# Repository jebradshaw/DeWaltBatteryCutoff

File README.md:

# DeWaltBatteryCutoff
Please Note: This circuit is purely experimental. There has not been much testing on it - at all.

PCB using the RP2040 Pico microcontroller to monitor a 20V DeWalt battery and give an alarm and eventually shutoff the battery load to avoid deep discharging.

KiCAD PCB Design
I used the pico microcontroller KiCAD model from https://github.com/ncarandini/KiCad-RP-Pico, which is really nicely done!

The circuit uses a RP2040 Pico microcontroller to monitor the battery voltage from a buffered voltage divider on an ADC pin.  The user must turn on the board with an external temporary pushbutton and power MOSFET turns on supplying voltage to the regulator that turns on the pico microcontroller.  The Pico then latches the MOSFET on and begins to run the voltage monitoring program. When the battery reaches a set value (can be stored in EEPROM) a buzzer alarm begins to sound, getting more rapid as the battery voltage approaches the low voltage cutoff value.  Once that value is surpassed (with hysteresis) a 10 second timer begins and the output voltage is cutoff using a P-Channel MOSFET (currently using a 27 amp version FRP27P06) where the pico turns itself off.  Data is transmitted over the USB port at 115200 baud and eeprom values can be set and saved.  Output format is a serial ASCII string with the following format:

NAME, TIME, rate of discharge, battery voltage, Buzzer critical state, high voltage alarm, low voltage alarm

"PICOBATMON,T:3412691,dVdT:0.000,Bv:20.24,Bcrit:0,Halarm:17.50,Lalarm:17.00\r\n"

The control program was written using the Arduino IDE with the Raspberry Pi Pico/RP2040 board library.  The user can set and save specific parameters in the EEPROM such as voltage, gain (resistor divider ratio), and a brief description (string).

Schematic of microcontroller circuit above.  PDF of Schematic can be downloaded here-> [PicoDeWalt_BattMonV2 Schematic.pdf](https://github.com/jebradshaw/DeWaltBatteryCutoff/files/11053368/PicoDeWalt_BattMonV2.Schematic.pdf)
 .

These printed circuit boards were made using Digikeys DK Red service and I am very happy with the results.

 To do list:  
   1. Turn on and off debugging through serial output terminal
   2. Implement Checksum?

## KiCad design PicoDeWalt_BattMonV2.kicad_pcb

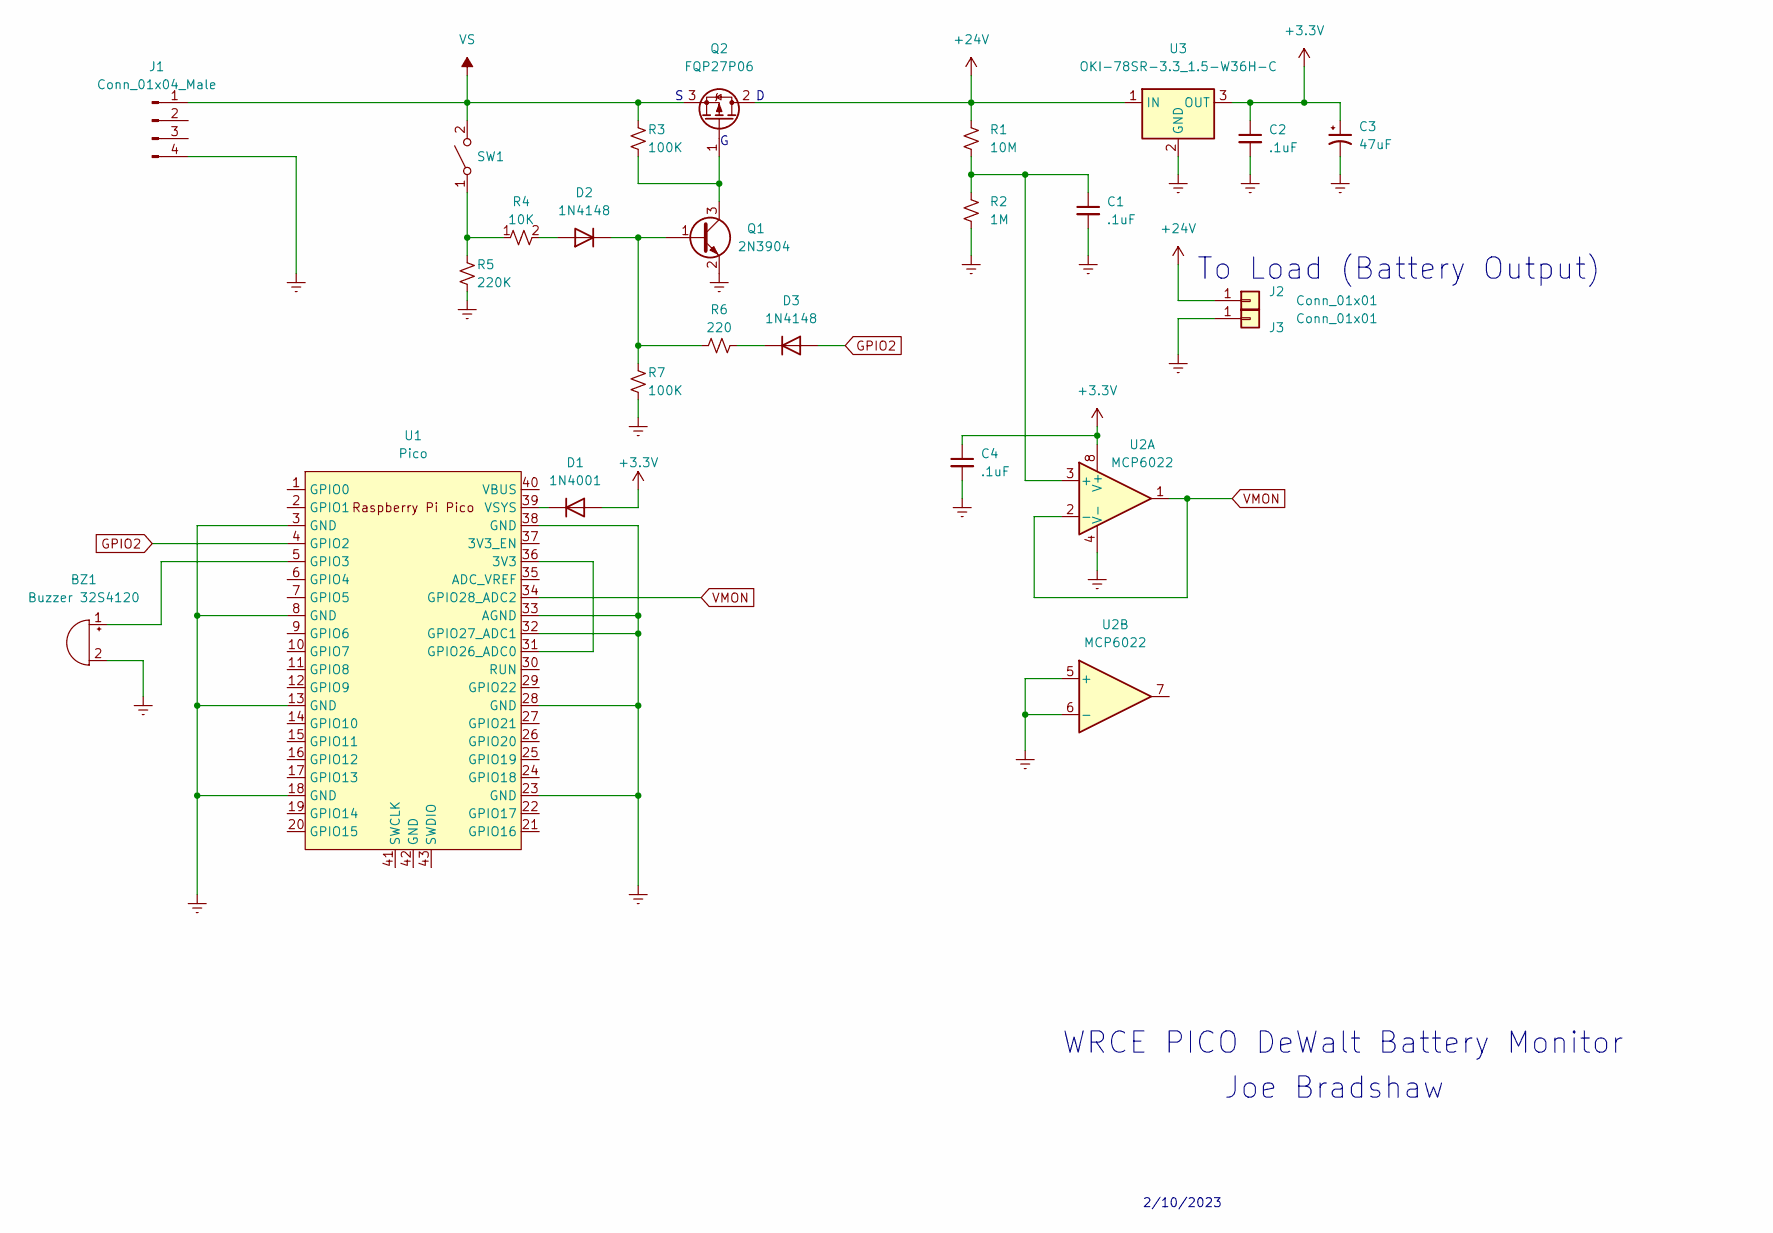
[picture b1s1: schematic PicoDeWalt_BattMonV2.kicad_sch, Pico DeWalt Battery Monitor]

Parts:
BZ1: Buzzer 32S4120; Buzzer_12x9.5RM7.6
C1, C4: .1uF; C_0805_2012Metric
C2: .1uF; C_0805_2012Metric_Pad1.18x1.45mm_HandSolder
C3: 47uF; CP_Elec_6.3x5.4_Nichicon
D1: 1N4001; D_DO-41_SOD81_P10.16mm_Horizontal
D2, D3: 1N4148; D_DO-35_SOD27_P7.62mm_Horizontal
J1: Conn_01x04_Male; DeWalt_battery_20V_Footprint
J2, J3: Conn_01x01; PowerPole_PCBmount_RA
Q1: 2N3904; SOT-23
Q2: FQP27P06; TO-220-3_Horizontal_TabDown
R1: 10M; R_0805_2012Metric
R2: 1M; R_0805_2012Metric
R3, R7: 100K; R_0805_2012Metric
R4: 10K; R_0805_2012Metric
R5: 220K; R_0805_2012Metric
R6: 220; R_0805_2012Metric
SW1: SW_SPST; JST_XH_B2B-XH-A_1x02_P2.50mm_Vertical
U1: Pico; RPi_Pico_SMD_TH
U2: MCP6022; SOIC-8_3.9x4.9mm_P1.27mm
U3: OKI-78SR-3.3_1.5-W36H-C; Converter_DCDC_Murata_OKI-78SR_Horizontal

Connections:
+3.3V: C2.1, C3.1, C4.1, D1.2 (A), U2.8 (V+), U3.3 (OUT)
+24V: J2.1, Q2.2 (D), R1.1, U3.1 (IN)
Earth: BZ1.2 (+), C1.2, C2.2, C3.2, C4.2, J1.4, J3.1, Q1.2 (E), R2.2, R5.2, R7.2, U1.3 (GND), U1.8 (GND), U1.13 (GND), U1.18 (GND), U1.23 (GND), U1.28 (GND), U1.32 (GPIO27_ADC1), U1.33 (AGND), U1.38 (GND), U2.4 (V-), U2.5 (+), U2.6 (-), U3.2 (GND)
GPIO2: D3.2 (A), U1.4 (GPIO2)
unnamed: BZ1.1 (-), U1.5 (GPIO3)
unnamed: C1.1, R1.2, R2.1, U2.3 (+)
unnamed: D1.1 (K), U1.39 (VSYS)
unnamed: D2.1 (K), Q1.1 (B), R6.1, R7.1
unnamed: D2.2 (A), R4.2
unnamed: D3.1 (K), R6.2
unnamed: Q1.3 (C), Q2.1 (G), R3.2
unnamed: R4.1, R5.1, SW1.1 (A)
unnamed: U1.31 (GPIO26_ADC0), U1.36 (3V3)
VMON: U1.34 (GPIO28_ADC2), U2.1, U2.2 (-)
VS: J1.1, Q2.3 (S), R3.1, SW1.2 (B)

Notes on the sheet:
2/10/2023
Joe Bradshaw
WRCE PICO DeWalt Battery Monitor
To Load (Battery Output)

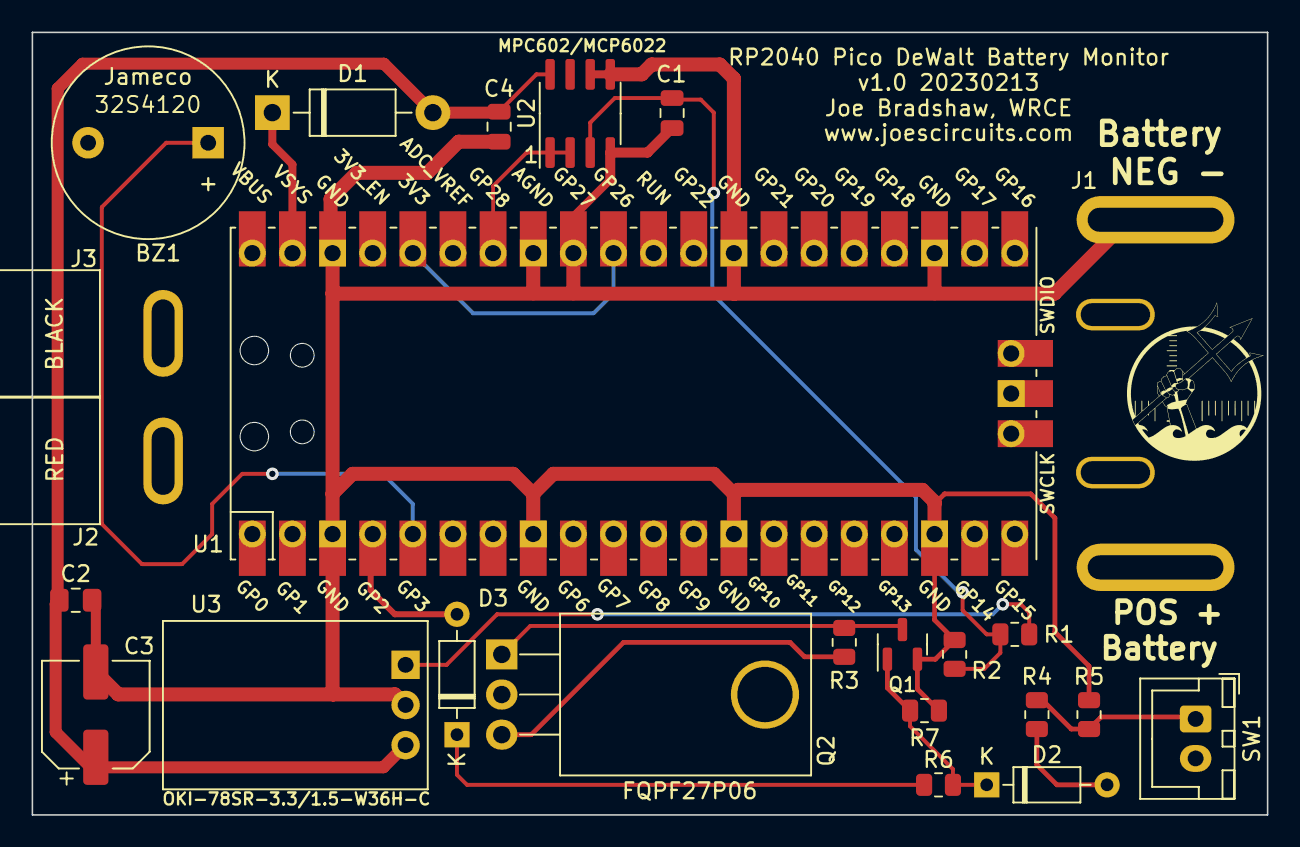
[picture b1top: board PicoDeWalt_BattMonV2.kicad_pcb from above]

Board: 2 copper layers, 78.2 x 49.5 mm, 24 parts (0 on the bottom side), 15 nets.

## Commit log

2023-11-06 Add files via upload
    added 'shutdown' serial command.
2023-11-06 Add files via upload
    KiCad PCB files uploaded
2023-11-06 Add files via upload
    External files for Anderson powerpole .STEP, DeWalt battery connector PCB footprint, WRCE logo, and RA powerpole PCB mount footprint.
2023-11-06 Add files via upload
    DeWalt_BatteryMon_Serial.py is a python example of reading the serial stream from the DeWalt battery monitor with a Raspberry Pi connected over USB as a serial device.
